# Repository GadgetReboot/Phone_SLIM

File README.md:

# Phone_SLIM
POTS Telephone Subscriber Line Interface Module
<br><br><BR><BR>
# Usage Notes
> [!NOTE]
> * This project is intended for hobby/personal use to explore how the plain old telephone service works.<br>
> * The PCB isn't designed to integrate with a live phone line. It is intended to create an offline system for local use.<br><br>

* It is recommended to add a TO-220 heat sink to the 3.3v regulator in case it gets too hot. I used [Wakefield-Vette 274-3AB](https://www.digikey.com/en/products/detail/wakefield-vette/274-3AB/2351871)  along with thermal paste and a nut/screw I had around.  <br>
* One pcb is needed for each phone/modem/etc.  One board has to have a jumper installed on J5 to act as a Server node and the other board(s) must have the jumper vacant to act as Sender nodes.<br>
* The Server board must connect to a WiFi router to function properly.  The SSID and Password for the router must be defined by editing the "arduino_secrets.h" file before compiling the sketch.<br>
* The telephone numbers are 7 digits long and are configured by editing the "project_globals.cpp" file and changing the numbers assigned to remotePhoneNumber and localPhoneNumber.<br>
* The region can be configured by uncommenting the desired line in the "project_globals.cpp" file, setting myRegion equal to North America or UK.<br><BR>

* Each board should be powered from an external 5 volt DC supply capable of 500mA since each board can draw several hundred mA.<BR>
* USB power can be used for programming and some testing, but the board may not be as stable as when powered externally.<BR>
* Set the power jumper J8 for USB or EXT as needed.<BR><BR>

# Parts
* The transformer is a 600:600 ohm audio isolation type.  The part used in the prototypes is from Ali Express, such as the red 4 pin ones here with description words such as EL14 included: https://s.click.aliexpress.com/e/_Dmlkp3z <BR><BR>

# Powering Up Two Nodes
* Power up the Server board first and wait for the blue LED to light up on the ESP module's built in LED to indicate it has joined the WiFi router.<br>
* Then power up the Sender board so it can try to auto-pair with the Server board over ESP-NOW.  In the future, software may be improved so the Sender board will auto-pair whenever the Server board is ready.<BR><BR>

* Check out this similar project being worked on: https://github.com/ktownsend-personal/RetroPhone
<br><br>
Shield: [![CC BY-SA 4.0][cc-by-sa-shield]][cc-by-sa]

This work is licensed under a
[Creative Commons Attribution-ShareAlike 4.0 International License][cc-by-sa].

[![CC BY-SA 4.0][cc-by-sa-image]][cc-by-sa]

[cc-by-sa]: http://creativecommons.org/licenses/by-sa/4.0/
[cc-by-sa-image]: https://licensebuttons.net/l/by-sa/4.0/88x31.png
[cc-by-sa-shield]: https://img.shields.io/badge/License-CC%20BY--SA%204.0-lightgrey.svg

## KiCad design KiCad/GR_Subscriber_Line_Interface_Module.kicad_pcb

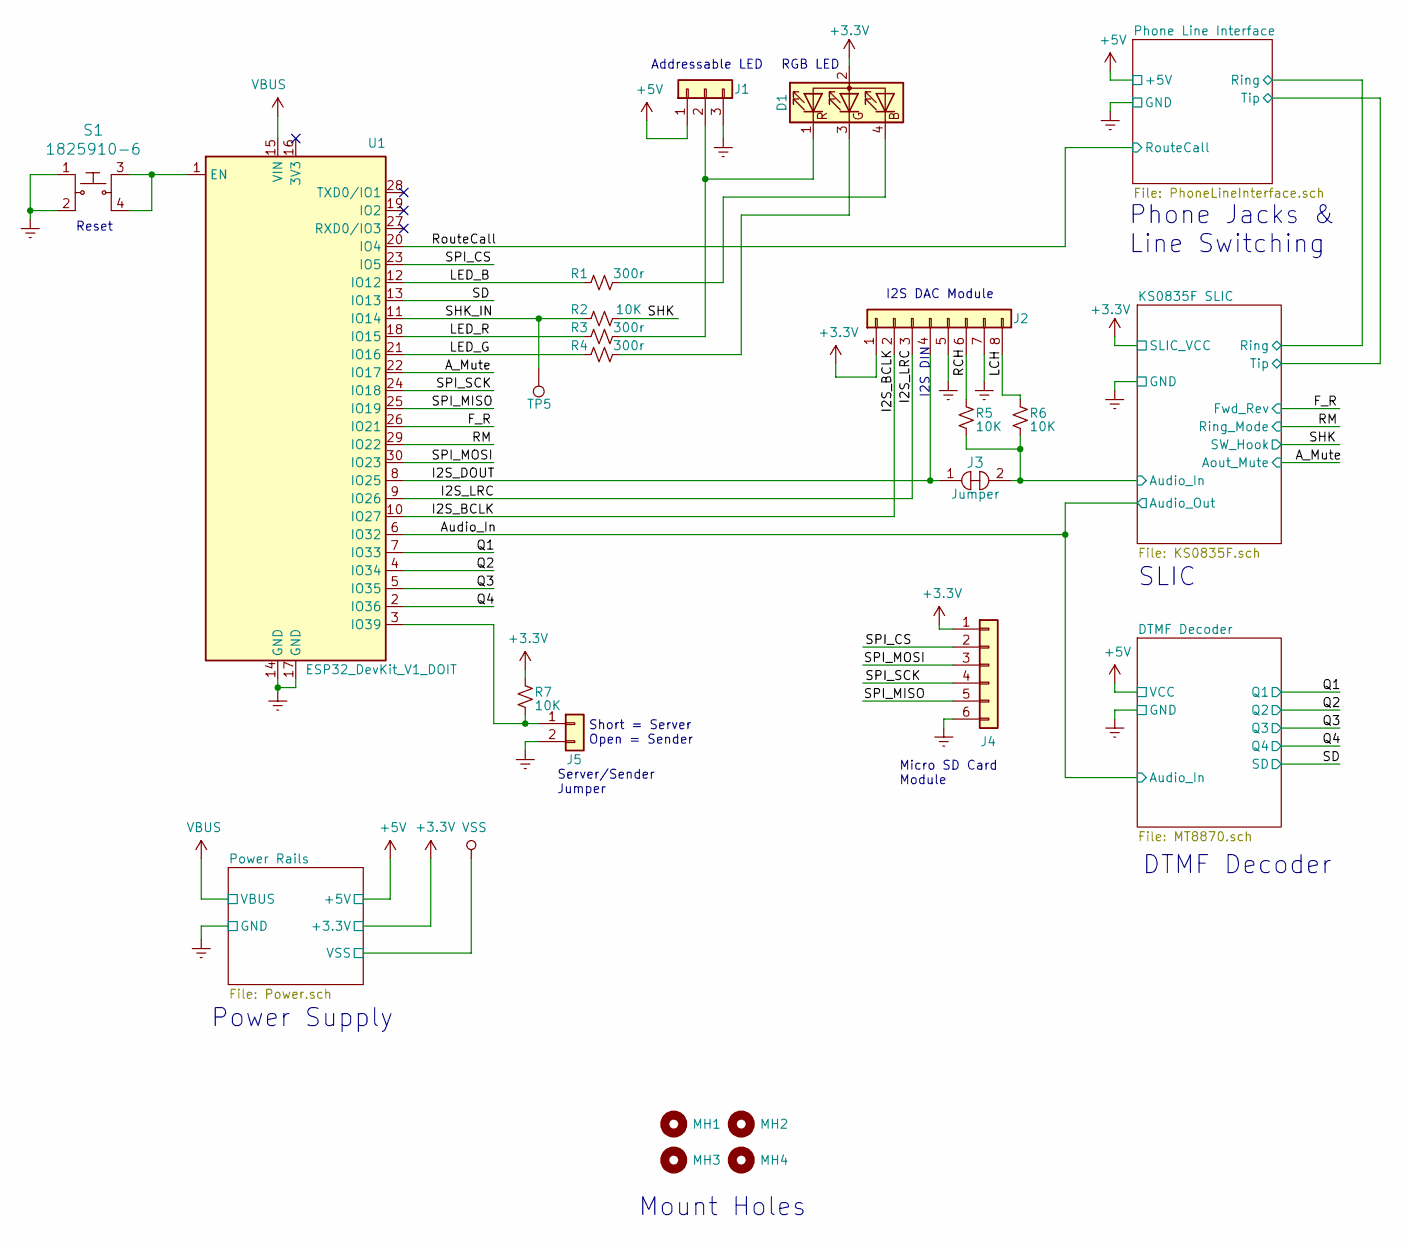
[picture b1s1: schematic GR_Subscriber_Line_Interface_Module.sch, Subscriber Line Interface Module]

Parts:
D1: LED_RAGB; LED_D5.0mm-4_RGB
J1: Conn_01x03; PinHeader_1x03_P2.54mm_Vertical
J2: Conn_01x08; PinHeader_1x08_P2.54mm_Vertical
J3: Jumper; SolderJumper-2_P1.3mm_Bridged_Pad1.0x1.5mm
J4: Conn_01x06; PinHeader_1x06_P2.54mm_Vertical
J5: Conn_01x02; PinHeader_1x02_P2.54mm_Vertical
MH1, MH2, MH3, MH4: MountingHole; MountingHole_3.2mm_M3
R1, R3, R4: 300r; R_Axial_DIN0207_L6.3mm_D2.5mm_P10.16mm_Horizontal
R2, R5, R6, R7: 10K; R_Axial_DIN0207_L6.3mm_D2.5mm_P10.16mm_Horizontal
S1: 1825910-6; Switch_Tactile_THT_6x6mm; MPN 1825910-6; Digi-Key_PN 450-1650-ND
TP5: TestPoint; TestPoint_Loop_D2.60mm_Drill1.4mm_Beaded
U1: ESP32_DevKit_V1_DOIT; esp32_devkit_v1_doit

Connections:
+3V3: D1.2 (A), J2.1, J4.1, R7.2; also elsewhere on the board
+5V: J1.1; also elsewhere on the board
/A_Mute: U1.22 (IO17); also elsewhere on the board
/Audio_In: U1.6 (IO32); also elsewhere on the board
/F_R: U1.26 (IO21); also elsewhere on the board
/I2S_BCLK: J2.2, U1.10 (IO27)
/I2S_DOUT: J2.4, J3.1, U1.8 (IO25)
/I2S_LRC: J2.3, U1.9 (IO26)
/KS0835F SLIC/Audio_In: J3.2, R5.1, R6.1; also elsewhere on the board
/LCH: J2.8, R6.2
/LED_B: R1.1, U1.12 (IO12)
/LED_G: R4.1, U1.21 (IO16)
/LED_R: R3.1, U1.18 (IO15)
/Q1: U1.7 (IO33); also elsewhere on the board
/Q2: U1.4 (IO34); also elsewhere on the board
/Q3: U1.5 (IO35); also elsewhere on the board
/Q4: U1.2 (IO36); also elsewhere on the board
/RCH: J2.6, R5.2
/RM: U1.29 (IO22); also elsewhere on the board
/RouteCall: U1.20 (IO4); also elsewhere on the board
/SD: U1.13 (IO13); also elsewhere on the board
/SHK: R2.2; also elsewhere on the board
/SHK_IN: R2.1, TP5.1, U1.11 (IO14)
/SPI_CS: J4.2, U1.23 (IO5)
/SPI_MISO: J4.5, U1.25 (IO19)
/SPI_MOSI: J4.3, U1.30 (IO23)
/SPI_SCK: J4.4, U1.24 (IO18)
GNDREF: J1.3, J2.5, J2.7, J4.6, J5.2, S1.1, S1.2, U1.14 (GND), U1.17 (GND); also elsewhere on the board
unnamed: D1.1 (RK), J1.2, R3.2
unnamed: D1.3 (GK), R4.2
unnamed: D1.4 (BK), R1.2
unnamed: J5.1, R7.1, U1.3 (IO39)
unnamed: S1.3, S1.4, U1.1 (EN)
VBUS: U1.15 (VIN); also elsewhere on the board

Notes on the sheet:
Mount Holes
DTMF Decoder
SLIC
Phone Jacks & Line Switching
Short = Server Open = Sender
Server/Sender Jumper
Power Supply
I2S DAC Module
Micro SD Card Module
Addressable LED
RGB LED
Reset
I2S DIN

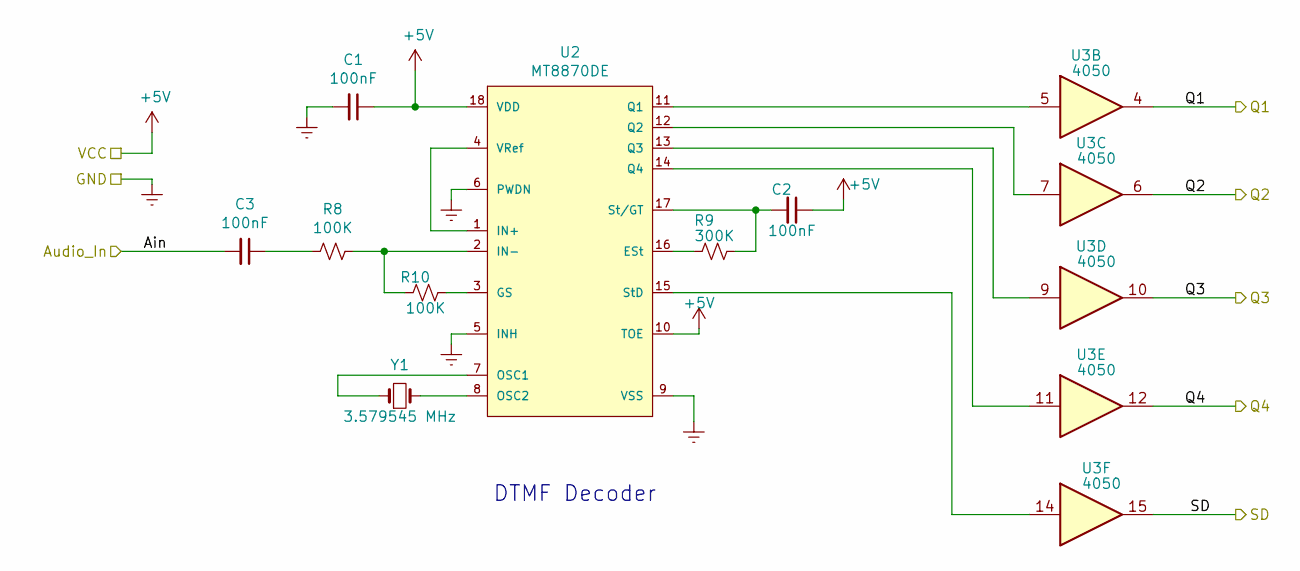
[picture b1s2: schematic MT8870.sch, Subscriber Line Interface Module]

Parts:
C1, C2, C3: 100nF; C_Disc_D4.3mm_W1.9mm_P5.00mm
R8, R10: 100K; R_Axial_DIN0207_L6.3mm_D2.5mm_P10.16mm_Horizontal
R9: 300K; R_Axial_DIN0207_L6.3mm_D2.5mm_P10.16mm_Horizontal
U2: MT8870DE; DIP-18_W7.62mm_Socket
U3: 4050; DIP-16_W7.62mm_Socket_LongPads
Y1: 3.579545 MHz; Crystal_HC49-4H_Vertical

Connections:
+5V: C1.1, C2.1, U2.10 (TOE), U2.18 (VDD); also elsewhere on the board
/Audio_In: C3.2; also elsewhere on the board
/Q1: U3.4; also elsewhere on the board
/Q2: U3.6; also elsewhere on the board
/Q3: U3.10; also elsewhere on the board
/Q4: U3.12; also elsewhere on the board
/SD: U3.15; also elsewhere on the board
GNDREF: C1.2, U2.5 (INH), U2.6 (PWDN), U2.9 (VSS); also elsewhere on the board
unnamed: C2.2, R9.1, U2.17 (St/GT)
unnamed: C3.1, R8.2
unnamed: R9.2, U2.16 (ESt)
unnamed: R10.1, U2.3 (GS)
unnamed: R8.1, R10.2, U2.2 (IN-)
unnamed: U2.1 (IN+), U2.4 (VRef)
unnamed: U2.7 (OSC1), Y1.1
unnamed: U2.8 (OSC2), Y1.2
unnamed: U2.11 (Q1), U3.5
unnamed: U2.12 (Q2), U3.7
unnamed: U2.13 (Q3), U3.9
unnamed: U2.14 (Q4), U3.11
unnamed: U2.15 (StD), U3.14

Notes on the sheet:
DTMF Decoder

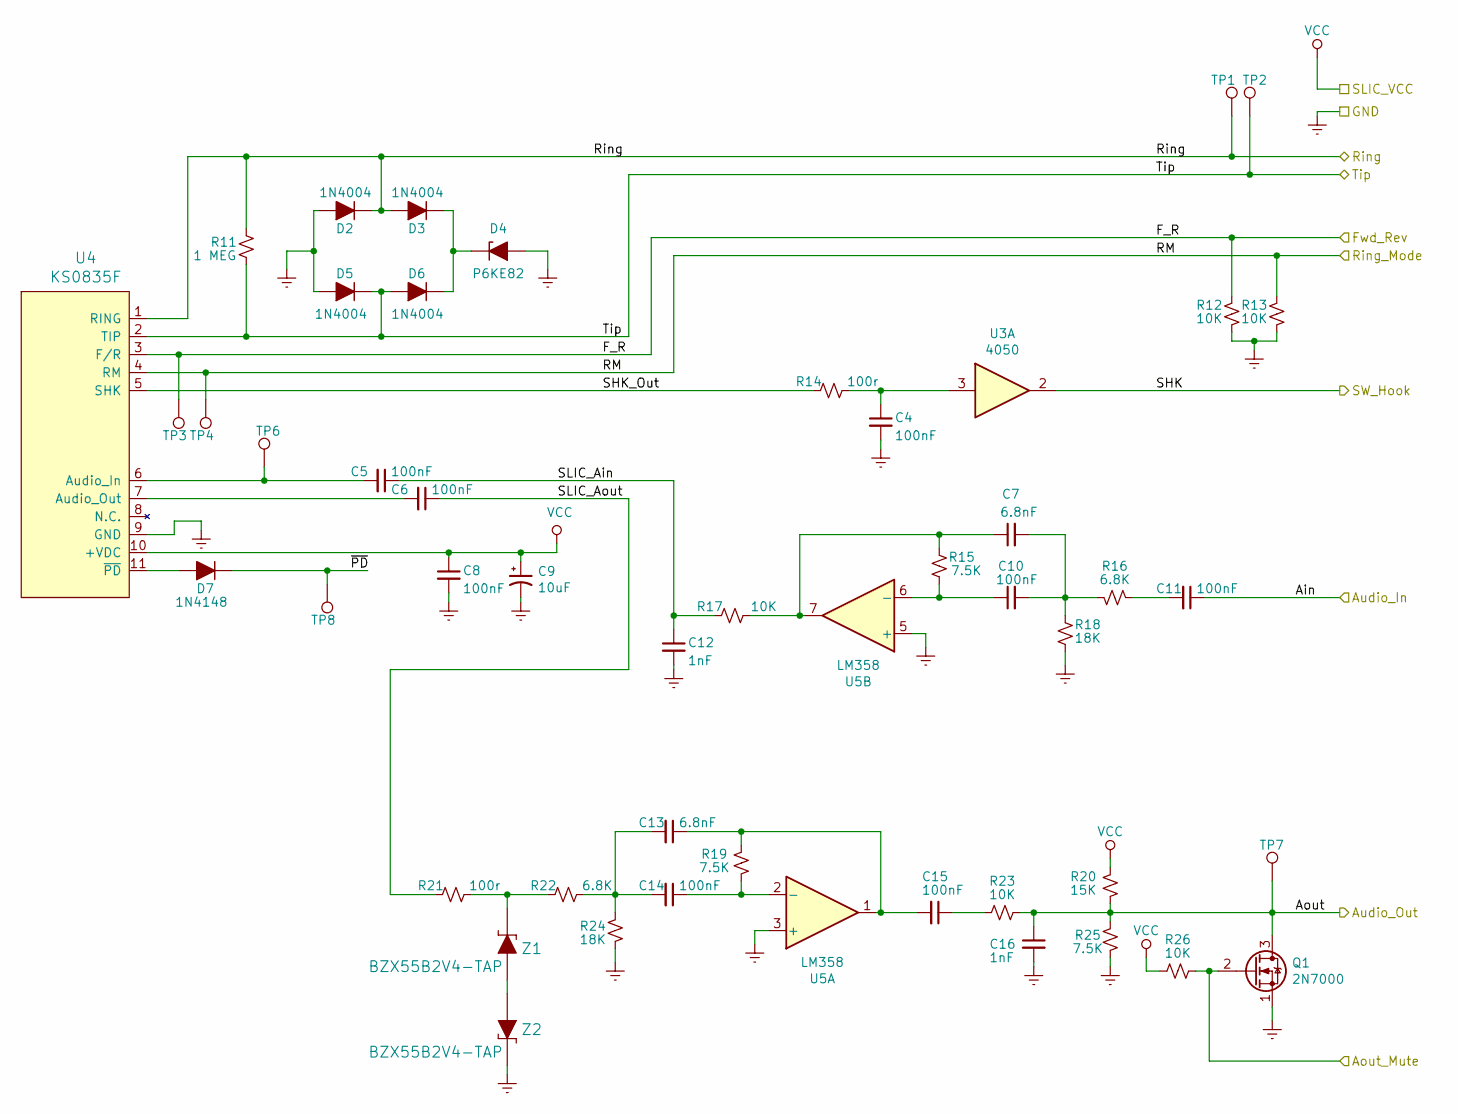
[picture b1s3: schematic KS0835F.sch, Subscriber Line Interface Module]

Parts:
C4, C5, C6, C8, C10, C11, C14, C15: 100nF; C_Disc_D4.3mm_W1.9mm_P5.00mm
C7, C13: 6.8nF; C_Disc_D4.3mm_W1.9mm_P5.00mm
C9: 10uF; CP_Radial_D5.0mm_P2.50mm
C12, C16: 1nF; C_Disc_D4.3mm_W1.9mm_P5.00mm
D2, D3, D5, D6: 1N4004; D_DO-41_SOD81_P10.16mm_Horizontal
D4: P6KE82; D_DO-41_SOD81_P10.16mm_Horizontal
D7: 1N4148; D_DO-35_SOD27_P7.62mm_Horizontal
Q1: 2N7000; TO-92_Inline
R11: 1 MEG; R_Axial_DIN0207_L6.3mm_D2.5mm_P10.16mm_Horizontal
R12, R13, R17, R23, R26: 10K; R_Axial_DIN0207_L6.3mm_D2.5mm_P10.16mm_Horizontal
R14, R21: 100r; R_Axial_DIN0207_L6.3mm_D2.5mm_P10.16mm_Horizontal
R15, R19, R25: 7.5K; R_Axial_DIN0207_L6.3mm_D2.5mm_P10.16mm_Horizontal
R16, R22: 6.8K; R_Axial_DIN0207_L6.3mm_D2.5mm_P10.16mm_Horizontal
R18, R24: 18K; R_Axial_DIN0207_L6.3mm_D2.5mm_P10.16mm_Horizontal
R20: 15K; R_Axial_DIN0207_L6.3mm_D2.5mm_P10.16mm_Horizontal
TP1, TP2, TP3, TP4, TP6, TP7, TP8: TestPoint; TestPoint_Loop_D2.60mm_Drill1.4mm_Beaded
U3: 4050; DIP-16_W7.62mm_Socket_LongPads
U4: KS0835F
U5: LM358; DIP-8_W7.62mm_Socket
Z1, Z2: BZX55B2V4-TAP; DO-35

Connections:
+3V3: C8.1, C9.1, R20.1, R26.1, U4.10 (+VDC); also elsewhere on the board
/A_Mute: Q1.2 (G), R26.2; also elsewhere on the board
/Audio_In: C16.1, Q1.3 (D), R20.2, R23.2, R25.1, TP7.1; also elsewhere on the board
/F_R: R12.1, TP3.1, U4.3 (F/R); also elsewhere on the board
/KS0835F SLIC/Audio_In: C11.1; also elsewhere on the board
/KS0835F SLIC/Ring: D2.1 (K), D3.2 (A), R11.2, TP1.1, U4.1 (RING); also elsewhere on the board
/KS0835F SLIC/SHK_Out: R14.1, U4.5 (SHK)
/KS0835F SLIC/SLIC_Ain: C5.1, C12.1, R17.1
/KS0835F SLIC/SLIC_Aout: C6.1, R21.1
/KS0835F SLIC/Tip: D5.1 (K), D6.2 (A), R11.1, TP2.1, U4.2 (TIP); also elsewhere on the board
/KS0835F SLIC/~PD: D7.1 (K), TP8.1
/RM: R13.1, TP4.1, U4.4 (RM); also elsewhere on the board
/SHK: U3.2; also elsewhere on the board
GNDREF: C4.2, C8.2, C9.2, C12.2, C16.2, D2.2 (A), D4.2 (A), D5.2 (A), Q1.1 (S), R12.2, R13.2, R18.2, R24.2, R25.2, U4.9 (GND), U5.3 (+), U5.5 (+), Z2.K; also elsewhere on the board
unnamed: C4.1, R14.2, U3.3
unnamed: C5.2, TP6.1, U4.6 (Audio_In)
unnamed: C6.2, U4.7 (Audio_Out)
unnamed: C7.1, R15.1, R17.2, U5.7
unnamed: C10.1, R15.2, U5.6 (-)
unnamed: C7.2, C10.2, R16.2, R18.1
unnamed: C11.2, R16.1
unnamed: C13.1, C15.2, R19.1, U5.1
unnamed: C13.2, C14.2, R22.2, R24.1
unnamed: C14.1, R19.2, U5.2 (-)
unnamed: C15.1, R23.1
unnamed: D3.1 (K), D4.1 (K), D6.1 (K)
unnamed: D7.2 (A), U4.11 (~PD)
unnamed: R21.2, R22.1, Z1.K
unnamed: Z1.A, Z2.A

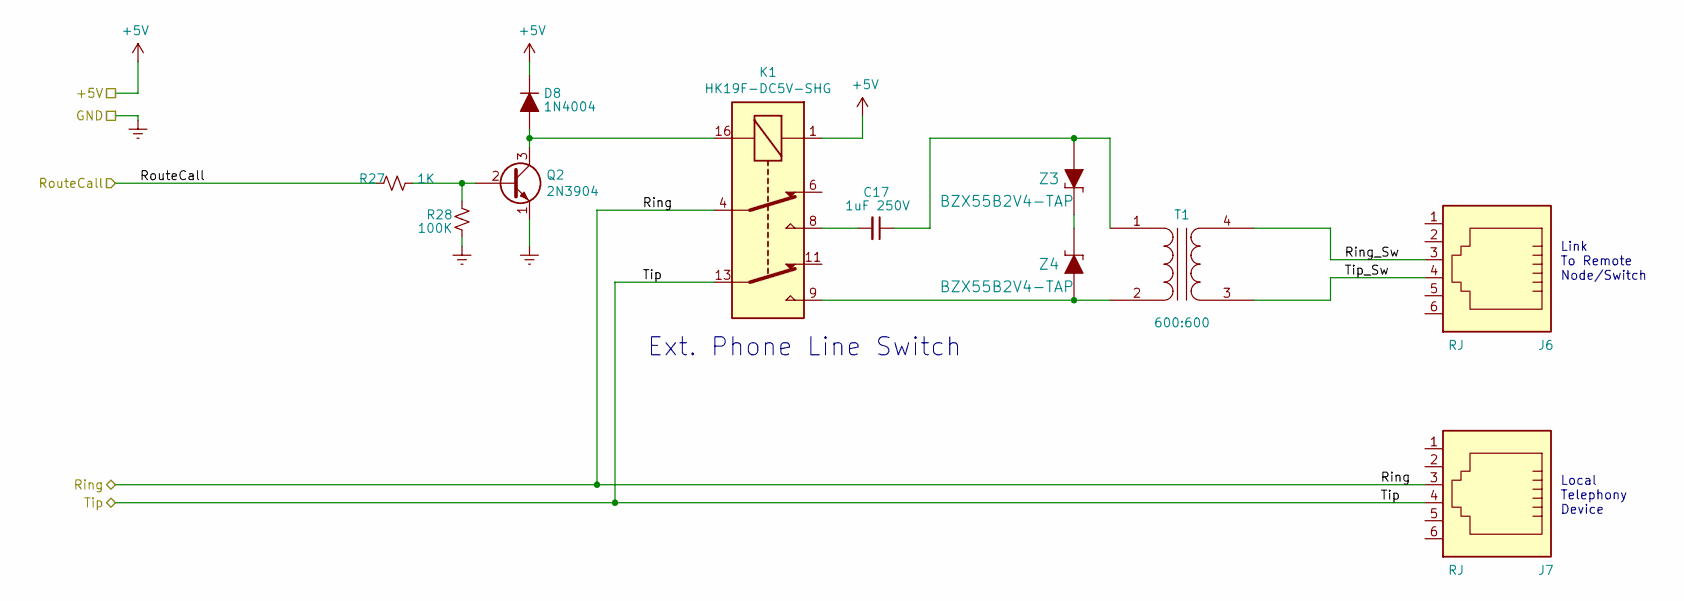
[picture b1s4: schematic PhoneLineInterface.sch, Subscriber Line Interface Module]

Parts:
C17: 1uF 250V; C_Rect_L16.5mm_W5.0mm_P15.00mm_MKT
D8: 1N4004; D_DO-41_SOD81_P10.16mm_Horizontal
J6, J7: RJ; RJ_6p6c; MFR P/N R-RJ11R06P-A800
K1: HK19F-DC5V-SHG; Relay_DPDT_Omron_G5V-2; MFR P/N HK19F-DC5V-SHG
Q2: 2N3904; TO-92_Inline_Wide
R27: 1K; R_Axial_DIN0207_L6.3mm_D2.5mm_P10.16mm_Horizontal
R28: 100K; R_Axial_DIN0207_L6.3mm_D2.5mm_P10.16mm_Horizontal
T1: 600:600; Transformer_600_600; MFR P/N EL14
Z3, Z4: BZX55B2V4-TAP; DO-35

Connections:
+5V: D8.1 (K), K1.1; also elsewhere on the board
/KS0835F SLIC/Ring: J7.3, K1.4; also elsewhere on the board
/KS0835F SLIC/Tip: J7.4, K1.13; also elsewhere on the board
/Phone Line Interface/Ring_Sw: J6.3, T1.4 (SB)
/Phone Line Interface/Tip_Sw: J6.4, T1.3 (SA)
/RouteCall: R27.1; also elsewhere on the board
GNDREF: Q2.1 (E), R28.1; also elsewhere on the board
unnamed: C17.1, T1.1 (AA), Z3.A
unnamed: C17.2, K1.8
unnamed: D8.2 (A), K1.16, Q2.3 (C)
unnamed: K1.9, T1.2 (AB), Z4.A
unnamed: Q2.2 (B), R27.2, R28.2
unnamed: Z3.K, Z4.K

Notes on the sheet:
Link To Remote Node/Switch
Ext. Phone Line Switch
Local Telephony Device

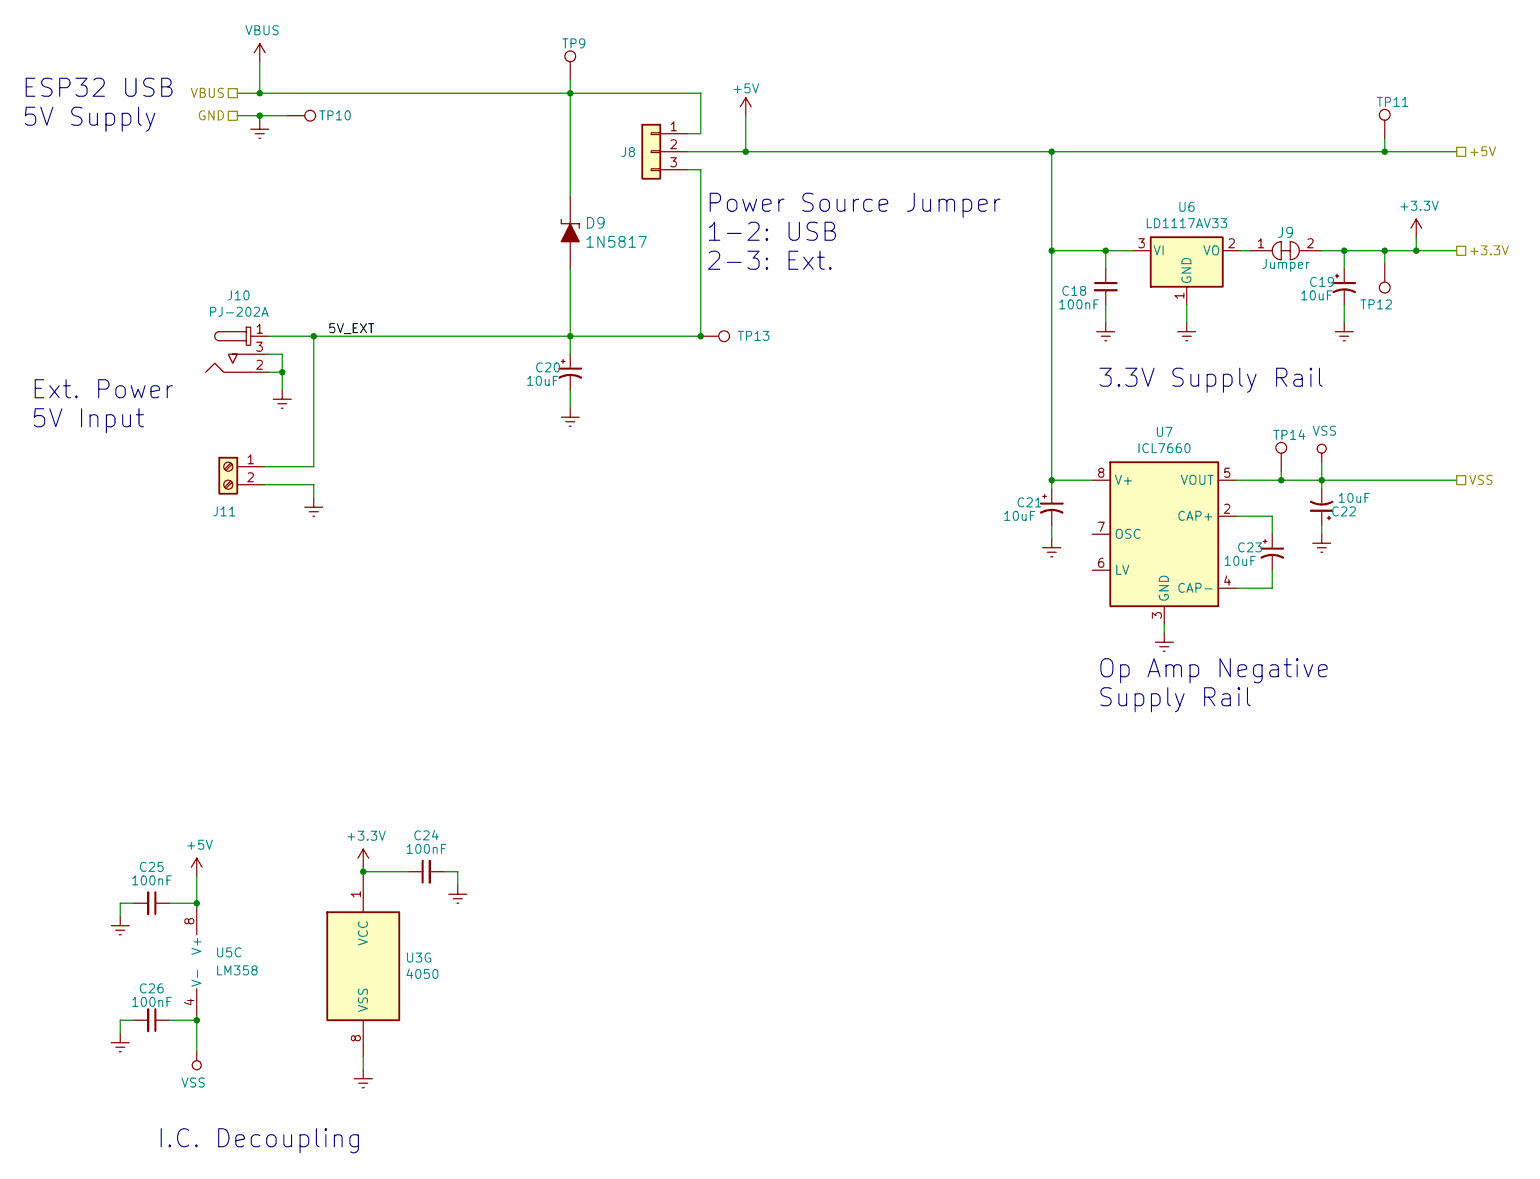
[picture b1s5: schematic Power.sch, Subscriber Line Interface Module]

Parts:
C18, C24, C25, C26: 100nF; C_Disc_D4.3mm_W1.9mm_P5.00mm
C19, C20, C21, C22, C23: 10uF; CP_Radial_D5.0mm_P2.50mm
D9: 1N5817; DO-41; MPN 1N5817; Digi-Key_PN 1N5817FSCT-ND
J8: Conn_01x03; PinHeader_1x03_P2.54mm_Vertical
J9: Jumper; SolderJumper-2_P1.3mm_Bridged_Pad1.0x1.5mm
J10: PJ-202A; Barrel_Jack_5.5mmODx2.1mmID_PJ-202A; MPN PJ-202A; Digi-Key_PN CP-202A-ND
J11: Screw_Terminal_01x02; TerminalBlock_bornier-2_P5.08mm
TP9, TP10, TP11, TP12, TP13, TP14: TestPoint; TestPoint_Loop_D2.60mm_Drill1.4mm_Beaded
U3: 4050; DIP-16_W7.62mm_Socket_LongPads
U5: LM358; DIP-8_W7.62mm_Socket
U6: LD1117AV33; TO-220-3_Vertical
U7: ICL7660; DIP-8_W7.62mm_Socket

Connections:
+3V3: C19.1, C24.1, J9.2, TP12.1, U3.1 (VCC); also elsewhere on the board
+5V: C18.1, C21.1, C25.1, J8.2, TP11.1, U5.8 (V+), U6.3 (VI), U7.8 (V+); also elsewhere on the board
/Power Rails/5V_EXT: C20.1, D9.A, J8.3, J10.1, J11.1, TP13.1
GNDREF: C18.2, C19.2, C20.2, C21.2, C22.1, C24.2, C25.2, C26.2, J10.2, J10.3, J11.2, TP10.1, U3.8 (VSS), U6.1 (GND), U7.3 (GND); also elsewhere on the board
unnamed: C23.1, U7.2 (CAP+)
unnamed: C23.2, U7.4 (CAP-)
unnamed: J9.1, U6.2 (VO)
VBUS: D9.K, J8.1, TP9.1; also elsewhere on the board
VSS: C22.2, C26.1, TP14.1, U5.4 (V-), U7.5 (VOUT)

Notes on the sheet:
Power Source Jumper 1-2: USB 2-3: Ext.
Op Amp Negative Supply Rail
Ext. Power 5V Input
3.3V Supply Rail
I.C. Decoupling
ESP32 USB 5V Supply

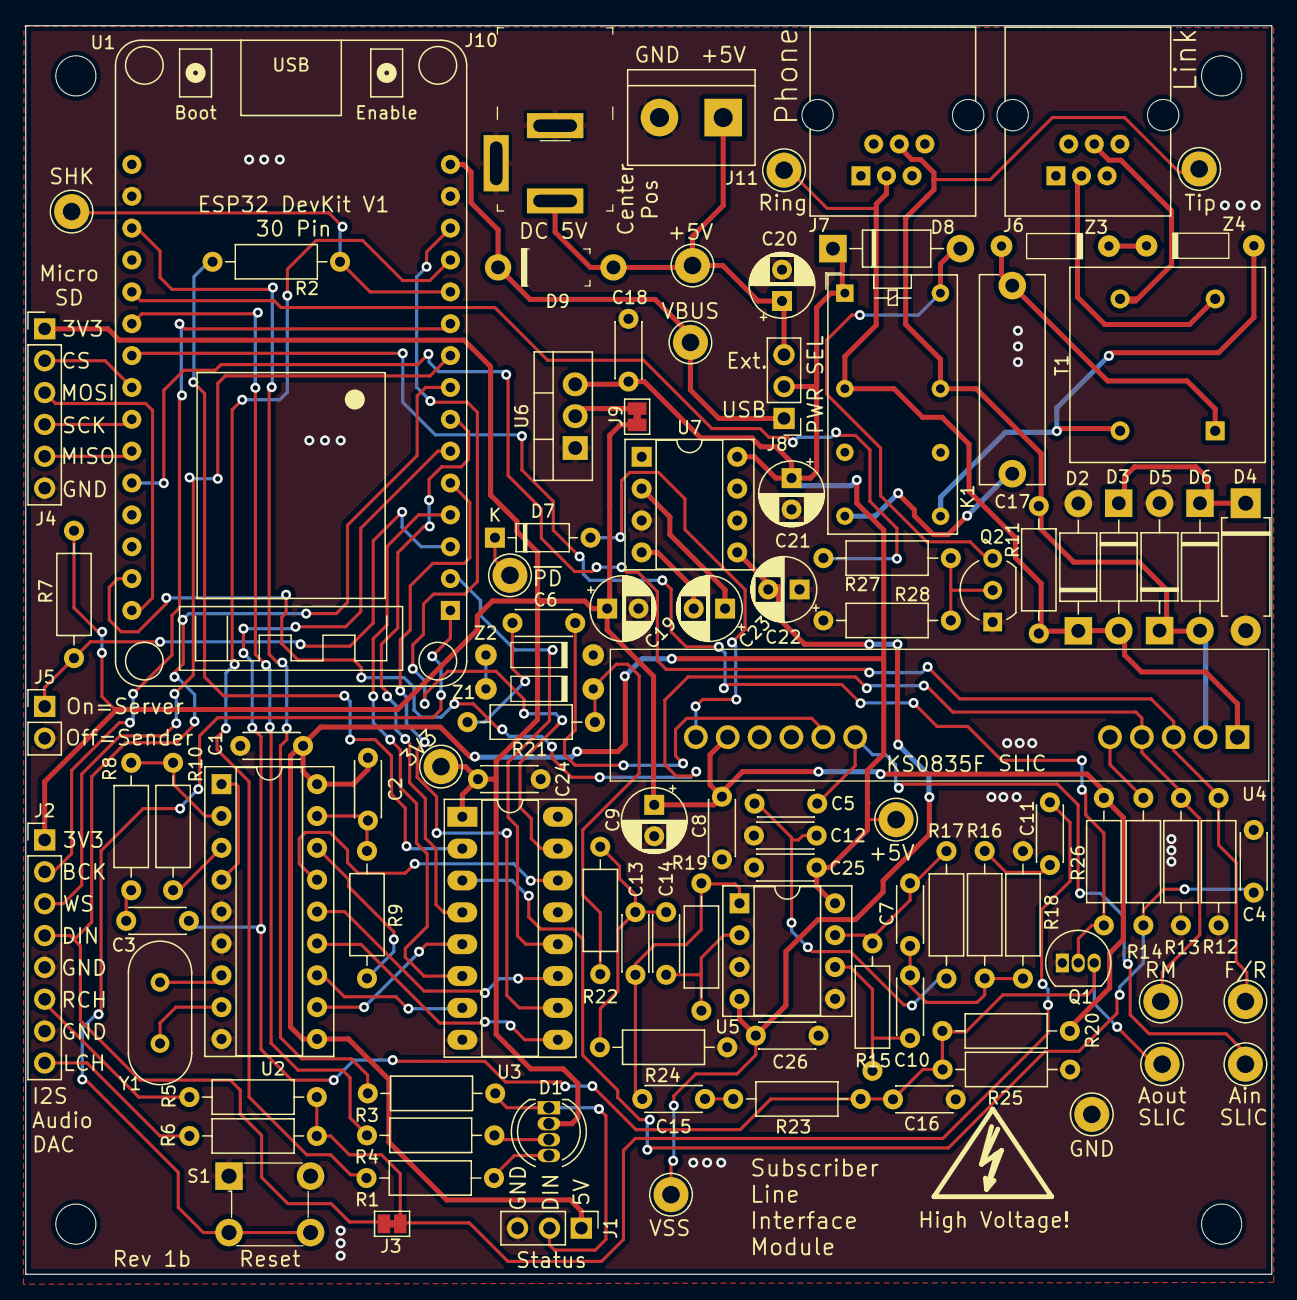
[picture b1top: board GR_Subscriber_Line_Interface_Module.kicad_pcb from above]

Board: 2 copper layers, 99.3 x 99.5 mm, 109 parts (0 on the bottom side), 81 nets.

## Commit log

2023-11-12 Create LICENSE
